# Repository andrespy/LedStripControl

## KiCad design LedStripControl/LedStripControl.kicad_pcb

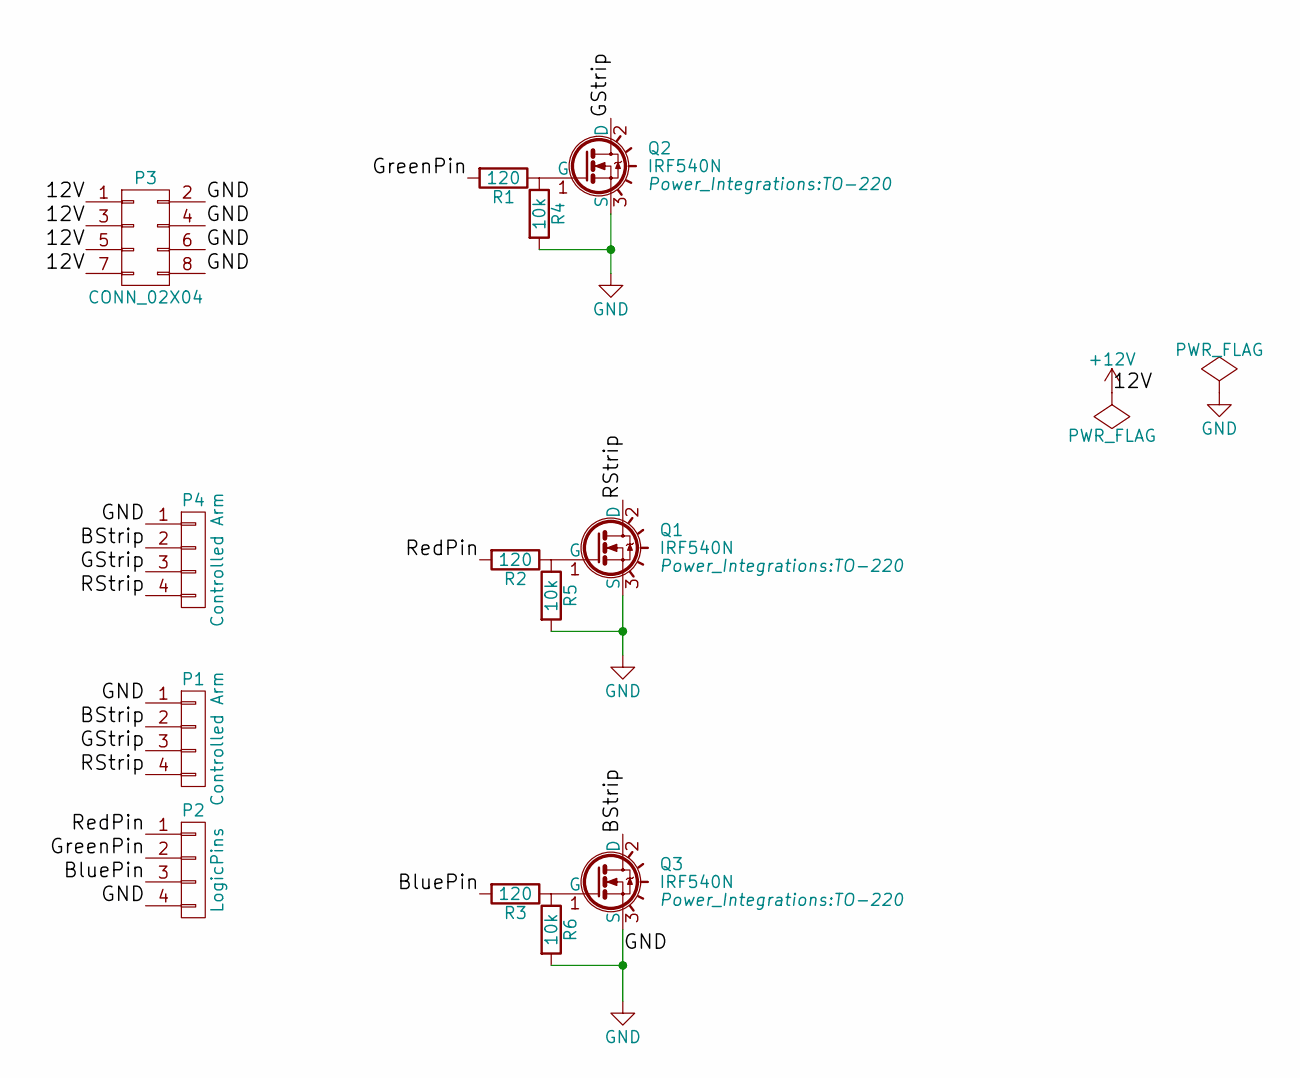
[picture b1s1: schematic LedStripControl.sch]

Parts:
P1, P4: Controlled Arm; Pin_Header_Straight_1x04_Pitch2.54mm
P2: LogicPins; Pin_Header_Straight_1x04_Pitch2.54mm
P3: CONN_02X04; Pin_Header_Straight_2x04_Pitch2.54mm
Q1, Q2, Q3: IRF540N; TO-220
R1, R2, R3: 120; R_Axial_DIN0207_L6.3mm_D2.5mm_P7.62mm_Horizontal
R4, R5, R6: 10k; R_Axial_DIN0207_L6.3mm_D2.5mm_P7.62mm_Horizontal

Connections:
+12V: P3.1, P3.3, P3.5, P3.7
/BStrip: P1.2, P4.2, Q3.2 (D)
/BluePin: P2.3, R3.2
/GStrip: P1.3, P4.3, Q2.2 (D)
/GreenPin: P2.2, R1.2
/RStrip: P1.4, P4.4, Q1.2 (D)
/RedPin: P2.1, R2.2
GND: P1.1, P2.4, P3.2, P3.4, P3.6, P3.8, P4.1, Q1.3 (S), Q2.3 (S), Q3.3 (S), R4.2, R5.2, R6.2
unnamed: Q1.1 (G), R2.1, R5.1
unnamed: Q2.1 (G), R1.1, R4.1
unnamed: Q3.1 (G), R3.1, R6.1

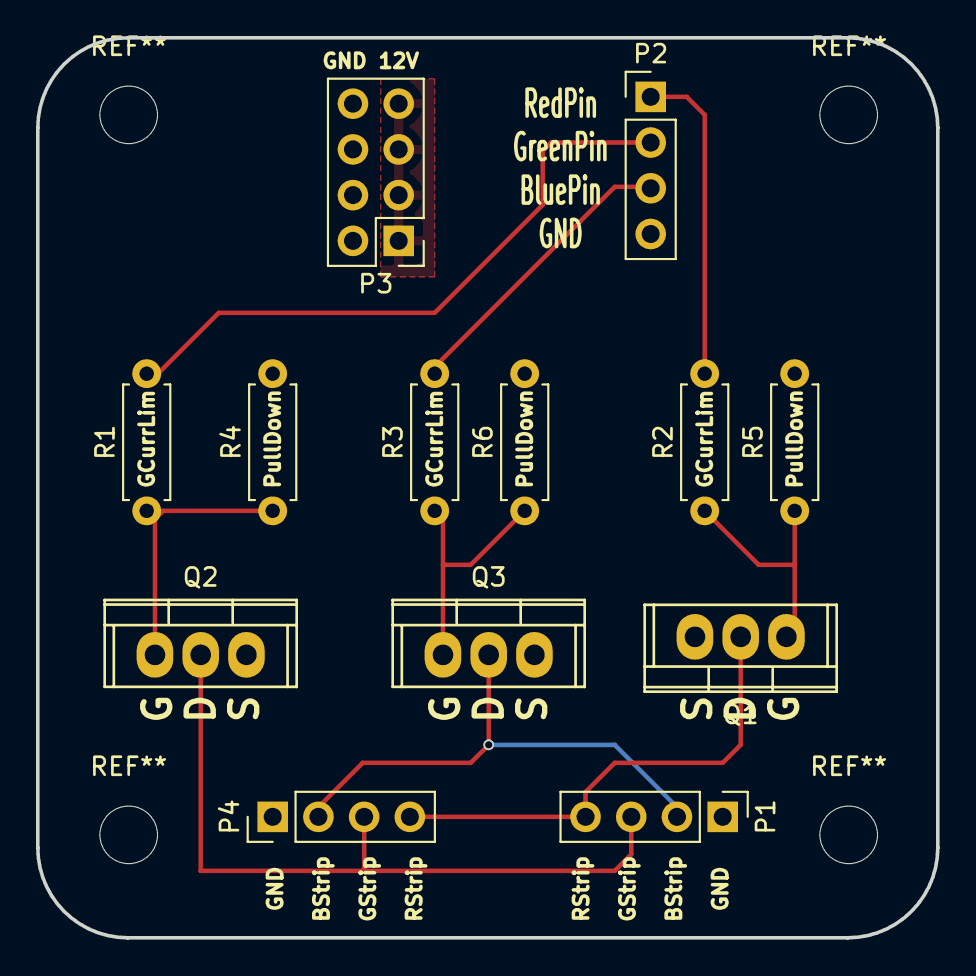
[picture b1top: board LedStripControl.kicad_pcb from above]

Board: 2 copper layers, 50.0 x 50.0 mm, 13 parts (0 on the bottom side), 11 nets.

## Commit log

2017-02-11 primer diseño sin rooting
2017-02-12 traces, ground and some other changes
